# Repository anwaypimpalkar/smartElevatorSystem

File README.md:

# Smart Elevator Systems using Embedded Machine Learning and Fire Safety Mechanisms

April - June 2021 | Micro Project in SY BTech

### Updates
- ***June 2021:** Awarded "Best Project" out of a pool of 1000+ projects at the 5th IEEE National Level Project Competition.*

- ***January 2022:** Check out the [Arduino Team's Blog Post](https://blog.arduino.cc/2022/01/29/this-contactless-system-combines-embedded-ml-and-sensors-to-improve-elevator-safety/?queryID=undefined) covering this project!*

## Introduction

Using an approach of Embedded Machine Learning, we built a multi-tenant architecture to facilitate a contactless elevator system. It consists of two parts – person detection and speech recognition. To create an effective pipeline, we used multiple signal processing techniques to extract necessary features from the input signals. Further, we developed a fire safety system using basic yet functional sensors in two methods – using a microcontroller and using an operational amplifier. These systems are deployed outside and inside an elevator, respectively. Lastly, we built a PCB to house all these components and make a holistically deployable product.

## High-Level Process Flow

First, we would want a person to come and stand in front of the elevator, indicating that he wants to use it. 
Then, the person would speak the floor number he would like to visit, and the elevator system recognizes the floor number which was spoken. The elevator then operates as it should and the doors should open for him. The overall flow of the system is shown in the figure below.

## System Overview

The project is a three-part system encompassing the following subsystems:

1. Person recognition (VWW Detection) and voice recognition (KWS) to operate the elevator.

2. Fire safety mechanism inside the elevator to drop installed oxygen masks and signal the main elevator interface.

3. Fire safety and detection system outside the elevator on different floors bundled with the features mentioned in point (1).

A generic block diagram of the entire system is shown below.

## Contactless Operation using KWS and VWW CNN Models

The KWS and VWW models are combined in a multi-tenant architecture. In such a structure, only one of the two models runs inference on the input data at a time. This allows for fast inferences and efficient memory allocation when and wherever required. As our development board of choice - *Arduino Nano 33 BLE Sense*, has limited resources available on board (1MB CPU Flash Memory, 256KB SRAM), the neural network on the system had to be memory and energy efficient compared to a whole scale neural network model. Further post-training quantization methods were implemented to reduce the size of the model (KWS model: 26,720 bytes; VWW model: 3,00,568 bytes; Total size after compilation: 207712 bytes 79% of dynamic memory) and latency of the inferences in real time.

#### Visual Wake Word (VWW) Model for Person Detection

The Visual Wake Word model used for our elevator use case is based on an existing MobileNets model. The core concept behind the architecture is depthwise separable convolution. This is a variant of classical two-dimensional convolutions that works in a much more efficient way, without compromising on accuracy greatly. The model has various steps, as shown in the figure below. Namely, these steps are Initialization, Pre-Processing, Model Inference, and Response.

#### Keyword Spotting (KWS) Model for Speech Recognition

To enable a completely contactless experience for the elevator interface, we implemented a speech recognition approach to choose the floor number that a given user would like to go to. We went on to implement a KWS (Keyword Spotting) model to satisfy this requirement. The chosen keywords were floor numbers in the lower order “One”, “Two”, “Three” and “Four”. Like the VWW model, the KWS model has 4 high level steps in the system as shown in the figure below. Compared to the prior, this model is relatively lightweight and takes lesser time for training and inference.

To make it easier for the CNN to process and classify the audio signals into different categories, we extract the features of the buffer audio sample before passing it into an inference pipeline. The various steps of feature extraction are:

- Fast Fourier Transform (FFT)
- Frequency Domain Spectrograms
- Mel Frequency Cepstral Coefficient Spectrograms

#### Multitenant Architecture for Running KWS and VWW Simultaneously

Due to the memory and power constraints on any embedded microcontroller, running two CNN inference engines simultaneously is a challenge. Our approach to this problem was to implement a multi-tenant architecture for combining the KWS and VWW model. In such a structure, only one of the two models runs inference on the input data at a time. Both models share the TensorArena and use the same memory allocations. This allowed for fast inferences and efficient memory allocation when and wherever required. There is also no requirement for the synchronization of data streams from the camera module and the microphone, both of which are running at different sampling rates.

## Fire Safety System

Elevator shafts may be exposed to smoke and that smoke could reach occupants not just inside the elevator but on other floors as well. In such situations, the elevator is advised to return to the ground floor of the building immediately. The most efficient way to develop a fire safety system which protects the occupants of an elevator is to design a system which works in tandem with it the smoke/flammable gas detectors and temperature sensors directly. To maximize the efficiency of such a system, we developed a pipeline in which the main elevator interface has direct inputs from the smoke detection units. Depending on the levels obtained from the sensors, the elevator interface can further be commanded to execute a specific set of instructions, for example taking the elevator to the lowest floor immediately in the case of a fire.

To implement our approach, we chose to use a MQ-2 Smoke/Flammable Gas Detector and a LM-35 Temperature sensor.

## Implementation and Results

The hardware required for the implementation of the contactless elevator system, i.e., the VWW and KWS models was readily available with us, namely the Arduino Nano 33 BLE Sense and OV7675 Camera Module. They are mounted on a shield for the scope of this experiment. Further into the implementation, we designed our own shield to house the OV7675 and Arduino module along with other peripherals.

Once the shield was properly positioned, we ran inference by standing inside and outside the frame of the camera. As discussed in the System Architecture chapter, each inference returns a probability value between -127 and +127, where higher numbers indicate a higher probability of a human subject being present in the frame.

The camera input of greyscale QCIF images of size 144 x 176 pixels with human subject are shown below.

Once the inference engine is run, the probability values are generated. These values are printed on the serial monitor of the Arduino IDE. When a person is entering the frame or in motion, the camera is unable to pick up the fast movement due to the low frame rate. At such moments, the model is decisive of whether a person is the frame or not. Hence, while classifying as a human detected in the field of view, we chose to keep a minimum Person score of 25. This threshold value reduces the number of false positives. If a person is detected in the frame, the green RGB light on the Arduino is lit up, whereas when there is no person detected, the red RGB light is lit up.

Once a person has been detected in the frame, the KWS model inference engine is triggered, and the system starts listening for keywords spoken by the user to communicate the floor number which they would like to go to. These numbers are chosen to be “One”, “Two”, “Three”, and “Four”. The incoming audio is sampled at 16 kHz and ran inference on every one second. Whenever the Arduino is listening for a keyword, the yellow light rapidly blinks, and upon positive inference, the blue RGB light is lit up. The different LED states are shown in the image below.

The fire safety system outside the elevator bundled with the deployed unit was simulated on Proteus. The system consisted of the following components:
1. MQ-2 Smoke Detector System
2. LM-35 Temperature Sensor
3. 7 Segment Display using Shift Register
4. Alarm and Connection to Main Elevator Interface

Since the Arduino Nano 33 BLE Sense was not available as a library for simulation, we used the Arduino Nano baseline model for it. The architecture is similar and hence is adequate for the purposes of the project. For the sake of completeness in the project, we chose to go create a pseudo-main elevator interface using an Arduino Uno in the simulation. A 4 x 16 LCD Display was also added for us to keep track of the system status. The figure below shows the circuit schematic for the project on Proteus. The Arduino Nano is interfaced with a LM-35 and MQ-2 sensor, a 7 Segment Display and an alarm system which is triggered when the system is simulating a fire scenario.

#### PCB Design

To house the components of this project, we created a Printed Circuit Board design using KiCAD, an open-source EDA software. Some key specifications of the PCB are:

1. The PCB consists of 4 Copper layers.

2. Front and Back Copper Layers are signal layers.
3. Inner1 Copper layer contains a Power Plane.
4. Inner2 Copper layer contains a Ground Plane.
5. All components used utilize Through Hole Technology (THT) except for 74AHC1G86 Dual Input Single Output EX-OR Gate which uses SMT.

## Demonstration

The hardware required was implemented as a proof of concept for the evaluation of the project. An unnarrated [video demonstration](https://youtu.be/mMH1OMFZL_I) has been documented.

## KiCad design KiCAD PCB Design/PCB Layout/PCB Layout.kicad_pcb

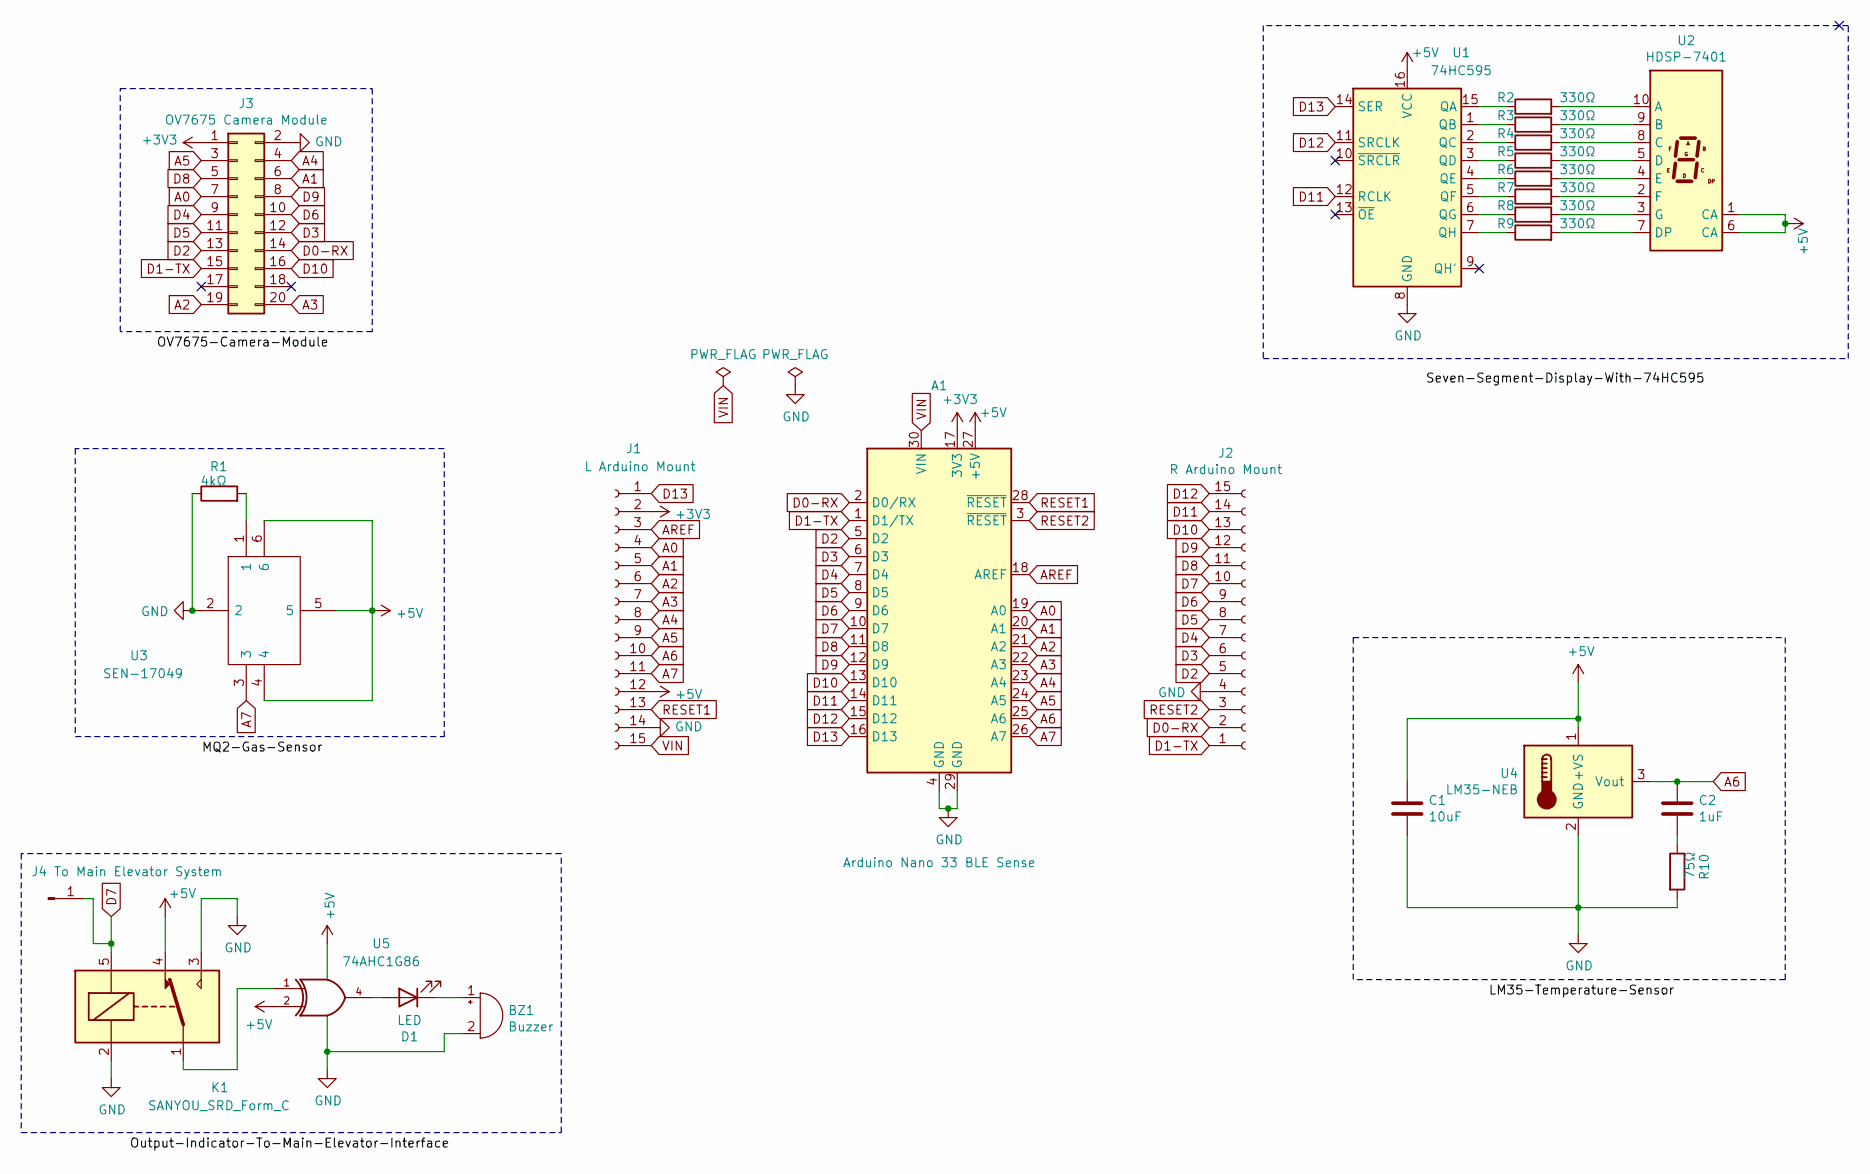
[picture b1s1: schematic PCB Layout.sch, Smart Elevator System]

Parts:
A1: Arduino Nano 33 BLE Sense; Arduino_Nano
BZ1: Buzzer; Buzzer_15x7.5RM7.6
C1: 10uF; C_Disc_D3.0mm_W1.6mm_P2.50mm
C2: 1uF; C_Disc_D3.0mm_W1.6mm_P2.50mm
D1: LED; LED_D5.0mm_FlatTop
J1: L Arduino Mount; PinSocket_1x15_P2.54mm_Vertical
J2: R Arduino Mount; PinSocket_1x15_P2.54mm_Vertical
J3: OV7675 Camera Module; PinSocket_2x10_P2.54mm_Vertical
J4: To Main Elevator System; PinHeader_1x01_P2.54mm_Vertical
K1: SANYOU_SRD_Form_C; Relay_SPDT_SANYOU_SRD_Series_Form_C
R1: 4kΩ; R_Axial_DIN0204_L3.6mm_D1.6mm_P7.62mm_Horizontal
R2, R3, R4, R5, R6, R7, R8, R9: 330Ω; R_Axial_DIN0204_L3.6mm_D1.6mm_P7.62mm_Horizontal
R10: 75Ω; R_Axial_DIN0204_L3.6mm_D1.6mm_P7.62mm_Horizontal
U1: 74HC595; DIP-16_W7.62mm
U2: HDSP-7401
U3: SEN-17049; SEN17049; Manufacturer_Part_Number SEN-17049
U4: LM35-NEB; TO-220-3_Vertical
U5: 74AHC1G86; SOT-23-5

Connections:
+3V3: A1.17 (3V3), J1.2, J3.1
+5V: A1.27 (+5V), C1.1, J1.12, K1.4, U1.16 (VCC), U2.1 (CA), U2.6 (CA), U3.4, U3.5, U3.6, U4.1 (+VS), U5.2, U5.5 (VCC)
A0: A1.19 (A0), J1.4, J3.7
A1: A1.20 (A1), J1.5, J3.6
A2: A1.21 (A2), J1.6, J3.19
A3: A1.22 (A3), J1.7, J3.20
A4: A1.23 (A4), J1.8, J3.4
A5: A1.24 (A5), J1.9, J3.3
A6: A1.25 (A6), C2.1, J1.10, U4.3 (Vout)
A7: A1.26 (A7), J1.11, U3.3
AREF: A1.18 (AREF), J1.3
D0-RX: A1.2 (D0/RX), J2.2, J3.14
D1-TX: A1.1 (D1/TX), J2.1, J3.15
D2: A1.5 (D2), J2.5, J3.13
D3: A1.6 (D3), J2.6, J3.12
D4: A1.7 (D4), J2.7, J3.9
D5: A1.8 (D5), J2.8, J3.11
D6: A1.9 (D6), J2.9, J3.10
D7: A1.10 (D7), J2.10, J4.1, K1.5
D8: A1.11 (D8), J2.11, J3.5
D9: A1.12 (D9), J2.12, J3.8
D10: A1.13 (D10), J2.13, J3.16
D11: A1.14 (D11), J2.14, U1.12 (RCLK)
D12: A1.15 (D12), J2.15, U1.11 (SRCLK)
D13: A1.16 (D13), J1.1, U1.14 (SER)
GND: A1.4 (GND), A1.29 (GND), BZ1.2 (+), C1.2, J1.14, J2.4, J3.2, K1.2, K1.3, R1.1, R10.2, U1.8 (GND), U3.2, U4.2 (GND), U5.3 (GND)
unnamed: BZ1.1 (-), D1.1 (K)
unnamed: C2.2, R10.1
unnamed: D1.2 (A), U5.4
unnamed: K1.1, U5.1
unnamed: R1.2, U3.1
unnamed: R2.1, U1.15 (QA)
unnamed: R2.2, U2.10 (A)
unnamed: R3.1, U1.1 (QB)
unnamed: R3.2, U2.9 (B)
unnamed: R4.1, U1.2 (QC)
unnamed: R4.2, U2.8 (C)
unnamed: R5.1, U1.3 (QD)
unnamed: R5.2, U2.5 (D)
unnamed: R6.1, U1.4 (QE)
unnamed: R6.2, U2.4 (E)
unnamed: R7.1, U1.5 (QF)
unnamed: R7.2, U2.2 (F)
unnamed: R8.1, U1.6 (QG)
unnamed: R8.2, U2.3 (G)
unnamed: R9.1, U1.7 (QH)
unnamed: R9.2, U2.7 (DP)
RESET1: A1.28 (~RESET), J1.13
RESET2: A1.3 (~RESET), J2.3
VIN: A1.30 (VIN), J1.15

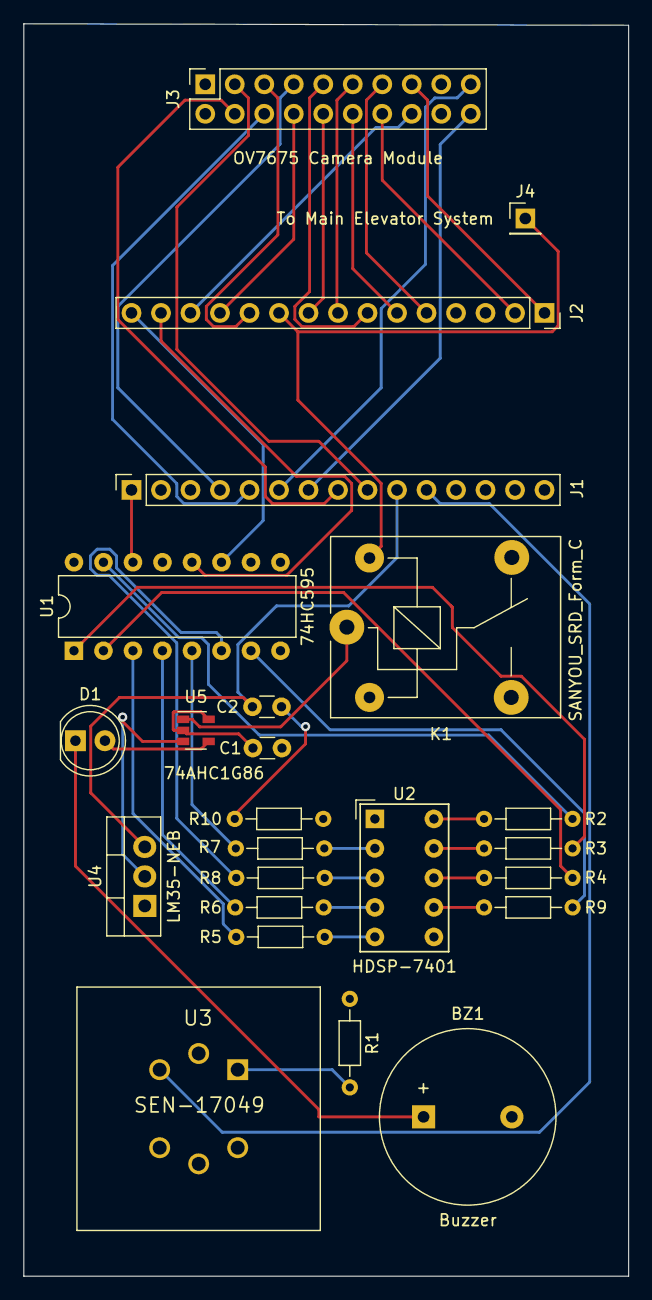
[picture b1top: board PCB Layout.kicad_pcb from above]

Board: 4 copper layers, 52.1 x 107.8 mm, 24 parts (0 on the bottom side), 46 nets.
